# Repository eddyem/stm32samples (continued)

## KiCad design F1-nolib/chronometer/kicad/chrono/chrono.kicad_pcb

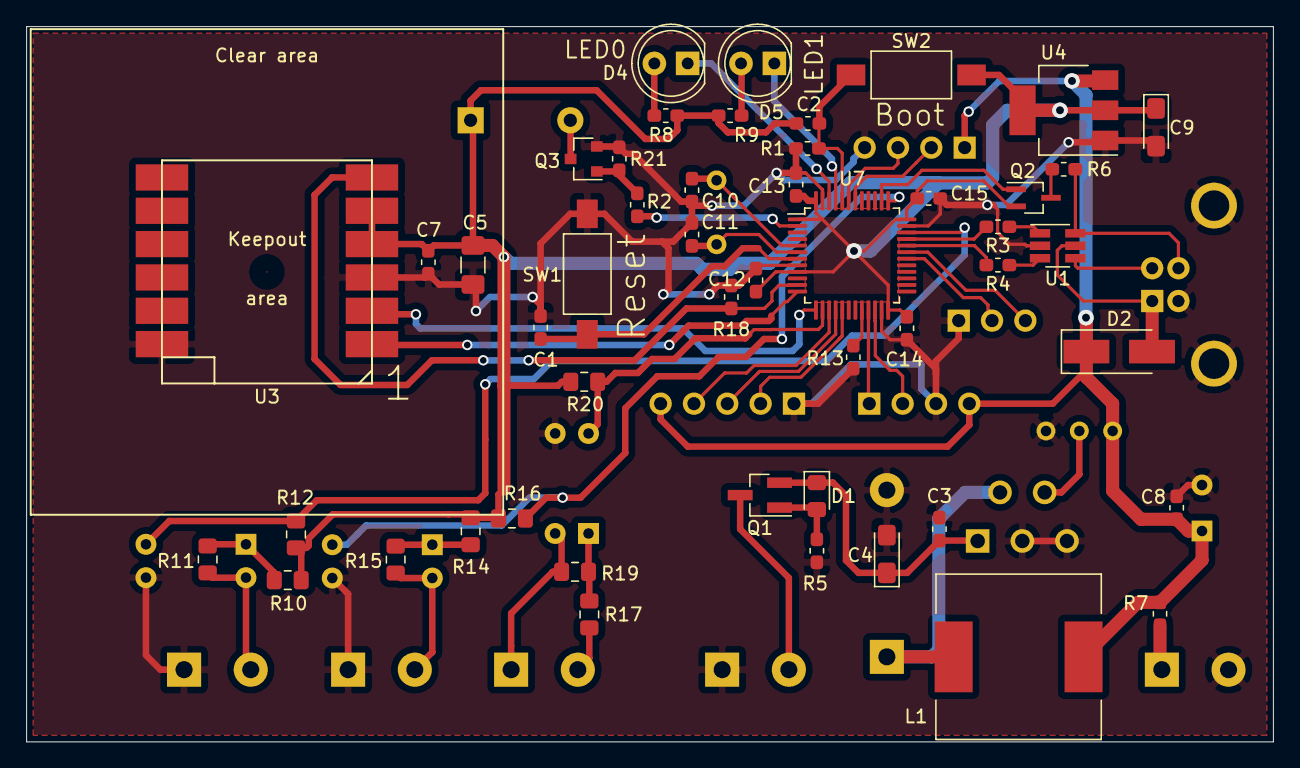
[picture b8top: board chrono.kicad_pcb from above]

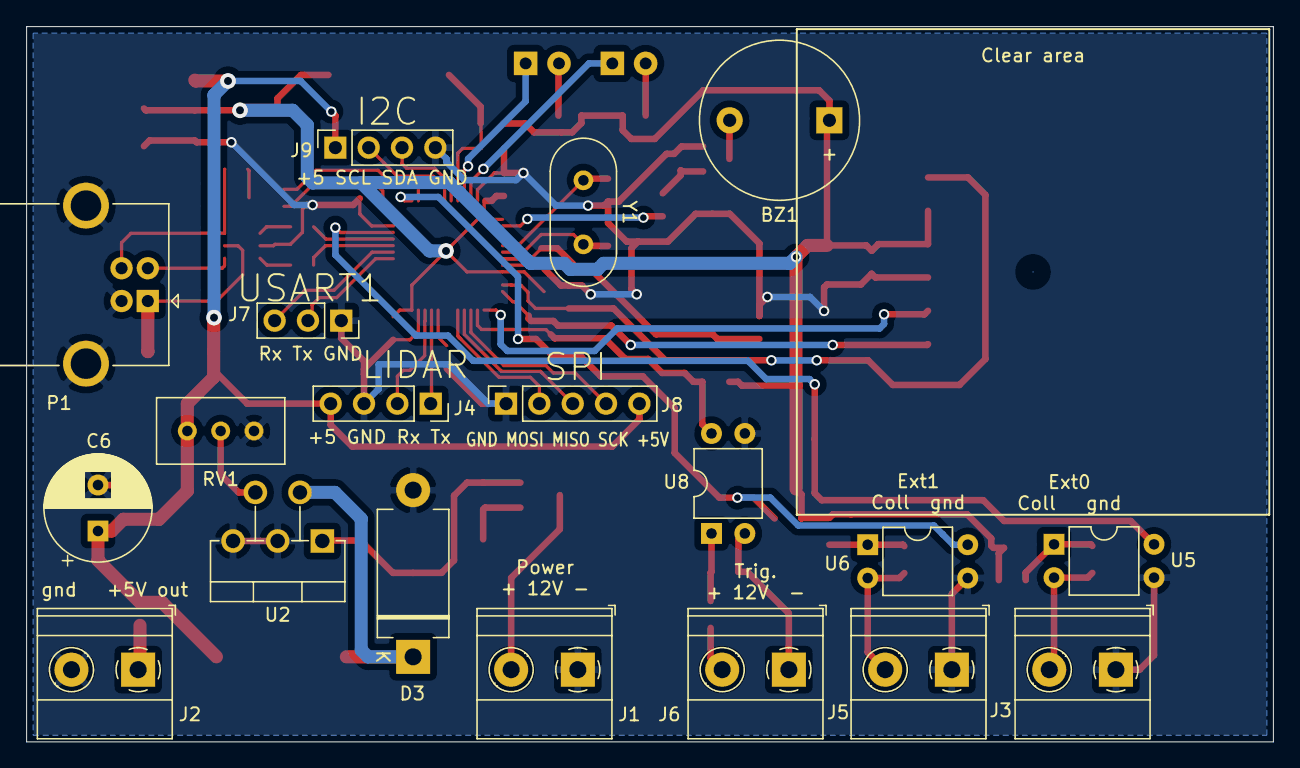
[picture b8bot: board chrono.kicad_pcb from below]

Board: 2 copper layers, 95.0 x 54.5 mm, 68 parts (19 on the bottom side), 52 nets.

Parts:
BZ1: Buzzer; Buzzer_12x9.5RM7.6
C1, C2, C3, C7, C8, C12, C13, C14, C15: 0.1; C_0603_1608Metric_Pad1.05x0.95mm_HandSolder
C4, C9: 47u; CP_EIA-3216-18_Kemet-A_Pad1.58x1.35mm_HandSolder
C5: 10u; C_1206_3216Metric_Pad1.42x1.75mm_HandSolder
C6: 100u; CP_Radial_D8.0mm_P3.50mm
C10, C11: 12; C_0603_1608Metric_Pad1.05x0.95mm_HandSolder
D1: MM3Z7V5; D_0805_2012Metric_Pad1.15x1.40mm_HandSolder
D2: SS14; D_SMA_Handsoldering
D3: 1n5822; D_DO-201_P12.70mm_Horizontal
D4: LED0; LED_D5.0mm
D5: LED1; LED_D5.0mm
J1: Power 12V; TerminalBlock_Phoenix_MKDS-1,5-2-5.08_1x02_P5.08mm_Horizont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
J2: +5Vout; TerminalBlock_Phoenix_MKDS-1,5-2-5.08_1x02_P5.08mm_Horizont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
J3: Ext_trig0; TerminalBlock_Phoenix_MKDS-1,5-2-5.08_1x02_P5.08mm_Horizont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
J4: LIDAR; PinSocket_1x04_P2.54mm_Vertical
J5: Ext_trig1; TerminalBlock_Phoenix_MKDS-1,5-2-5.08_1x02_P5.08mm_Horizont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
J6: Ext_trig2; TerminalBlock_Phoenix_MKDS-1,5-2-5.08_1x02_P5.08mm_Horizont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
J7: USART1; PinSocket_1x03_P2.54mm_Vertical
J8: SPI; PinSocket_1x05_P2.54mm_Vertical
J9: I2C1; PinSocket_1x04_P2.54mm_Vertical
L1: 100u; L_12x12mm_H4.5mm
P1: USB_B; USB_B_OST_USB-B1HSxx_Horizontal
Q1: AO3407; SOT-23_Handsoldering
Q2: DTA114Y; SOT-323_SC-70_Handsoldering
Q3: Q_NMOS_GSD; SOT-23
R1, R5, R21: 10k; R_0603_1608Metric_Pad1.05x0.95mm_HandSolder
R2: 510; R_0603_1608Metric_Pad1.05x0.95mm_HandSolder
R3, R4, R7: 22; R_0603_1608Metric_Pad1.05x0.95mm_HandSolder
R6: 1k5; R_0603_1608Metric_Pad1.05x0.95mm_HandSolder
R8, R9: 330; R_0603_1608Metric_Pad1.05x0.95mm_HandSolder
R10, R14: 330; R_0805_2012Metric_Pad1.15x1.40mm_HandSolder
R11, R12, R15, R16, R19, R20: 4k7; R_0805_2012Metric_Pad1.15x1.40mm_HandSolder
R13, R18: 100k; R_0603_1608Metric_Pad1.05x0.95mm_HandSolder
R17: 2k2; R_0805_2012Metric_Pad1.15x1.40mm_HandSolder
RV1: 10k; Potentiometer_Bourns_3296W_Vertical
SW1: Reset; SW_SPST_FSMSM
SW2: Boot; SW_SPST_FSMSM
U1: USBLC6-2SC6; SOT-23-6_Handsoldering
U2: LM2576ADJ; TO-220-5_P3.4x3.7mm_StaggerEven_Lead3.8mm_Vertical
U3: L80-R
U4: LM1117-3.3; SOT-223
U5, U6, U8: PC817; DIP-4_W7.62mm
U7: STM32F103C6Tx; LQFP-48_7x7mm_P0.5mm
Y1: 8MHz; Crystal_HC49-U_Vertical

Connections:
+3V3: BZ1.1, C2.2, C5.2, C7.2, C9.1, C12.2, C13.2, C14.2, C15.2, Q2.2, R8.2, R9.2, R10.2, R12.1, R14.2, R16.1, R20.1, SW2.2, U3.4, U3.5, U4.2, U4.4, U7.1, U7.9, U7.24, U7.36, U7.48
+5V: C6.1, C8.1, D2.1, J4.4, J8.5, J9.1, L1.1, R7.2, RV1.1, U4.3
/BOOT0: C2.1, R1.1, SW2.1, U7.44
/LED0: D4.1, U7.46
/LED1: D5.1, U7.45
/MISO: J8.3, U7.16
/MOSI: J8.2, U7.17
/NRST: C1.1, SW1.1, U7.7
/OSC_IN: C10.1, U7.5, Y1.1
/OSC_OUT: C11.1, U7.6, Y1.2
/PPS: R18.2, U3.6, U7.11
/SCK: J8.4, U7.15
/SCL: J9.2, U7.42
/SDA: J9.3, U7.43
/TRIG0: R12.2, U5.4, U7.34
/TRIG1: R16.2, U6.4, U7.37
/TRIG2: R20.2, U7.14, U8.4
/U1Rx: J7.3, U7.31
/U1Tx: J7.2, U7.30
/U2Rx: J4.2, U7.22
/U2Tx: J4.1, U7.21
/U3Rx: U3.2, U7.13
/U3Tx: U3.1, U7.12
/USBDM: R4.2, U7.32
/USBDP: R3.2, U7.33
/USB_PU: Q2.1, U7.38
/buzzer: R2.2, U7.2
GND: C1.2, C3.2, C4.2, C5.1, C6.2, C7.1, C8.2, C9.2, C10.2, C11.2, C12.1, C13.1, C14.1, C15.1, D3.2, J1.1, J2.2, J3.1, J4.3, J5.1, J7.1, J8.1, J9.4, P1.4, P1.5, Q3.2, R1.2, R5.1, R13.2, R18.1, R21.2, RV1.3, SW1.2, U1.2, U2.3, U2.5, U3.3, U3.12, U4.1, U5.3, U6.3, U7.8, U7.23, U7.35, U7.47, U8.3
unnamed: BZ1.2, Q3.3
unnamed: C3.1, C4.1, D1.1, Q1.2, U2.1
unnamed: D1.2, Q1.1, R5.2
unnamed: D2.2, P1.1, U1.5
unnamed: D3.1, L1.2, U2.2
unnamed: D4.2, R8.1
unnamed: D5.2, R9.1
unnamed: J1.2, Q1.3
unnamed: J2.1, R7.1
unnamed: J3.2, R11.1, U5.2
unnamed: J5.2, R15.1, U6.2
unnamed: J6.1, R19.1, U8.2
unnamed: J6.2, R17.1
unnamed: P1.2, U1.4
unnamed: P1.3, R6.2, U1.6
unnamed: Q2.3, R6.1
unnamed: Q3.1, R2.1, R21.1
unnamed: R3.1, U1.1
unnamed: R4.1, U1.3
unnamed: R10.1, R11.2, U5.1
unnamed: R13.1, U7.20
unnamed: R14.1, R15.2, U6.1
unnamed: R17.2, R19.2, U8.1
unnamed: RV1.2, U2.4

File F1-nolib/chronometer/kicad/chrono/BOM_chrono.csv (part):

"Source:","/home/eddy/Docs/SAO/ELECTRONICS/STM32/F1-srcs/chronometer/kicad/chrono/chrono.sch"
"Date:","÷Ô 09 ÉÀÌ 2019 08:40:12"
"Tool:","Eeschema (6.0.0-rc1-dev-1613-ga55d9819b)"
"Generator:","/usr/local/share/kicad/plugins/bom_csv_grouped_by_value.py"
"Component Count:","68"

"Individual Components:"

"Item","Qty","Reference(s)","Value","LibPart","Footprint","Datasheet","Manufacturer"
"","","BZ1","Buzzer","Device:Buzzer","Buzzer_Beeper:Buzzer_12x9.5RM7.6","~",""
"","","C1","0.1","stm32-rescue:C","Capacitor_SMD:C_0603_1608Metric_Pad1.05x0.95mm_HandSolder","",""
"","","C2","0.1","stm32-rescue:C","Capacitor_SMD:C_0603_1608Metric_Pad1.05x0.95mm_HandSolder","",""
"","","C3","0.1","stm32-rescue:C","Capacitor_SMD:C_0603_1608Metric_Pad1.05x0.95mm_HandSolder","",""
"","","C4","47u","stm32-rescue:CP","Capacitor_Tantalum_SMD:CP_EIA-3216-18_Kemet-A_Pad1.58x1.35mm_HandSolder","",""
"","","C5","10u","Device:C","Capacitor_SMD:C_1206_3216Metric_Pad1.42x1.75mm_HandSolder","~",""
"","","C6","100u","stm32-rescue:CP","Capacitor_THT:CP_Radial_D8.0mm_P3.50mm","",""
"","","C7","0.1","stm32-rescue:C","Capacitor_SMD:C_0603_1608Metric_Pad1.05x0.95mm_HandSolder","",""
"","","C8","0.1","stm32-rescue:C","Capacitor_SMD:C_0603_1608Metric_Pad1.05x0.95mm_HandSolder","",""
"","","C9","47u","stm32-rescue:CP","Capacitor_Tantalum_SMD:CP_EIA-3216-18_Kemet-A_Pad1.58x1.35mm_HandSolder","",""
"","","C10","12","stm32-rescue:C","Capacitor_SMD:C_0603_1608Metric_Pad1.05x0.95mm_HandSolder","",""
"","","C11","12","stm32-rescue:C","Capacitor_SMD:C_0603_1608Metric_Pad1.05x0.95mm_HandSolder","",""
"","","C12","0.1","stm32-rescue:C","Capacitor_SMD:C_0603_1608Metric_Pad1.05x0.95mm_HandSolder","",""
"","","C13","0.1","stm32-rescue:C","Capacitor_SMD:C_0603_1608Metric_Pad1.05x0.95mm_HandSolder","",""
"","","C14","0.1","stm32-rescue:C","Capacitor_SMD:C_0603_1608Metric_Pad1.05x0.95mm_HandSolder","",""
"","","C15","0.1","stm32-rescue:C","Capacitor_SMD:C_0603_1608Metric_Pad1.05x0.95mm_HandSolder","",""
"","","D1","MM3Z7V5","Device:D_Zener","Diode_SMD:D_0805_2012Metric_Pad1.15x1.40mm_HandSolder","~",""
"","","D2","SS14","Device:D_Schottky","Diode_SMD:D_SMA_Handsoldering","~",""
"","","D3","1n5822","stm32-rescue:D","Diode_THT:D_DO-201_P12.70mm_Horizontal","",""
"","","D4","LED0","stm32-rescue:LED-RESCUE-stm32","LED_THT:LED_D5.0mm","",""
"","","D5","LED1","stm32-rescue:LED-RESCUE-stm32","LED_THT:LED_D5.0mm","",""
"","","J1","Power 12V","Connector_Generic:Conn_01x02","TerminalBlock_Phoenix:TerminalBlock_Phoenix_MKDS-1,5-2-5.08_1x02_P5.08mm_Horizontal","~",""
"","","J2","+5Vout","Connector_Generic:Conn_01x02","TerminalBlock_Phoenix:TerminalBlock_Phoenix_MKDS-1,5-2-5.08_1x02_P5.08mm_Horizontal","~",""
"","","J3","Ext_trig0","Connector_Generic:Conn_01x02","TerminalBlock_Phoenix:TerminalBlock_Phoenix_MKDS-1,5-2-5.08_1x02_P5.08mm_Horizontal","~",""
"","","J4","LIDAR","Connector:Conn_01x04_Female","Connector_PinSocket_2.54mm:PinSocket_1x04_P2.54mm_Vertical","~",""
"","","J5","Ext_trig1","Connector_Generic:Conn_01x02","TerminalBlock_Phoenix:TerminalBlock_Phoenix_MKDS-1,5-2-5.08_1x02_P5.08mm_Horizontal","~",""
"","","J6","Ext_trig2","Connector_Generic:Conn_01x02","TerminalBlock_Phoenix:TerminalBlock_Phoenix_MKDS-1,5-2-5.08_1x02_P5.08mm_Horizontal","~",""
"","","J7","USART1","Connector:Conn_01x03_Female","Connector_PinSocket_2.54mm:PinSocket_1x03_P2.54mm_Vertical","~",""
"","","J8","SPI","Connector:Conn_01x05_Female","Connector_PinSocket_2.54mm:PinSocket_1x05_P2.54mm_Vertical","~",""
"","","J9","I2C1","Connector:Conn_01x04_Female","Connector_PinSocket_2.54mm:PinSocket_1x04_P2.54mm_Vertical","~",""
"","","L1","100u","stm32-rescue:L","Inductor_SMD:L_12x12mm_H4.5mm","",""
"","","P1","USB_B","stm32-rescue:USB_A-RESCUE-stm32","Connectors_USB:USB_B_OST_USB-B1HSxx_Horizontal","",""
"","","Q1","AO3407","stm32-rescue:Q_PMOS_GSD","TO_SOT_Packages_SMD:SOT-23_Handsoldering","",""
"","","Q2","DTA114Y","Transistor_BJT:DTA114Y","TO_SOT_Packages_SMD:SOT-323_SC-70_Handsoldering","",""
"","","Q3","Q_NMOS_GSD","Device:Q_NMOS_GSD","Package_TO_SOT_SMD:SOT-23","~",""
"","","R1","10k","stm32-rescue:R","Resistor_SMD:R_0603_1608Metric_Pad1.05x0.95mm_HandSolder","",""
"","","R2","510","Device:R","Resistor_SMD:R_0603_1608Metric_Pad1.05x0.95mm_HandSolder","~",""
"","","R3","22","stm32-rescue:R","Resistor_SMD:R_0603_1608Metric_Pad1.05x0.95mm_HandSolder","",""
"","","R4","22","stm32-rescue:R","Resistor_SMD:R_0603_1608Metric_Pad1.05x0.95mm_HandSolder","",""
"","","R5","10k","stm32-rescue:R","Resistor_SMD:R_0603_1608Metric_Pad1.05x0.95mm_HandSolder","",""
"","","R6","1k5","stm32-rescue:R","Resistor_SMD:R_0603_1608Metric_Pad1.05x0.95mm_HandSolder","",""
"","","R7","22","Device:R","Resistor_SMD:R_0603_1608Metric_Pad1.05x0.95mm_HandSolder","~",""
"","","R8","330","stm32-rescue:R","Resistor_SMD:R_0603_1608Metric_Pad1.05x0.95mm_HandSolder","",""
"","","R9","330","stm32-rescue:R","Resistor_SMD:R_0603_1608Metric_Pad1.05x0.95mm_HandSolder","",""
"","","R10","330","Device:R","Resistor_SMD:R_0805_2012Metric_Pad1.15x1.40mm_HandSolder","~",""
"","","R11","4k7","Device:R","Resistor_SMD:R_0805_2012Metric_Pad1.15x1.40mm_HandSolder","~",""
"","","R12","4k7","Device:R","Resistor_SMD:R_0805_2012Metric_Pad1.15x1.40mm_HandSolder","~",""
"","","R13","100k","stm32-rescue:R","Resistor_SMD:R_0603_1608Metric_Pad1.05x0.95mm_HandSolder","",""
"","","R14","330","Device:R","Resistor_SMD:R_0805_2012Metric_Pad1.15x1.40mm_HandSolder","~",""
"","","R15","4k7","Device:R","Resistor_SMD:R_0805_2012Metric_Pad1.15x1.40mm_HandSolder","~",""
"","","R16","4k7","Device:R","Resistor_SMD:R_0805_2012Metric_Pad1.15x1.40mm_HandSolder","~",""
"","","R17","2k2","Device:R","Resistor_SMD:R_0805_2012Metric_Pad1.15x1.40mm_HandSolder","~",""
"","","R18","100k","stm32-rescue:R","Resistor_SMD:R_0603_1608Metric_Pad1.05x0.95mm_HandSolder","",""
"","","R19","4k7","Device:R","Resistor_SMD:R_0805_2012Metric_Pad1.15x1.40mm_HandSolder","~",""
"","","R20","4k7","Device:R","Resistor_SMD:R_0805_2012Metric_Pad1.15x1.40mm_HandSolder","~",""
"","","R21","10k","Device:R","Resistor_SMD:R_0603_1608Metric_Pad1.05x0.95mm_HandSolder","~",""
"","","RV1","R_POT","Device:R_POT","Potentiometer_THT:Potentiometer_Bourns_3296W_Vertical","~",""
"","","SW1","Reset","Switch:SW_Push","Buttons_Switches_SMD:SW_SPST_FSMSM","",""
"","","SW2","Boot","Switch:SW_Push","Buttons_Switches_SMD:SW_SPST_FSMSM","",""
"","","U1","USBLC6-2SC6","Power_Protection:USBLC6-2SC6","TO_SOT_Packages_SMD:SOT-23-6_Handsoldering","http://www2.st.com/resource/en/datasheet/CD00050750.pdf",""
"","","U2","LM2576ADJ","stm32-rescue:LM2576HV","TO_SOT_Packages_THT:TO-220-5_P3.4x3.7mm_StaggerEven_Lead3.8mm_Vertical","","Texas Instruments"
"","","U3","L80-R","Chrono:L80-R","chrono:L80-R","",""
"","","U4","LM1117-3.3","stm32-rescue:LM1117-3.3-RESCUE-stm32","TO_SOT_Packages_SMD:SOT-223","",""
"","","U5","PC817","Isolator:PC817","Package_DIP:DIP-4_W7.62mm","http://www.soselectronic.cz/a_info/resource/d/pc817.pdf",""
"","","U6","PC817","Isolator:PC817","Package_DIP:DIP-4_W7.62mm","http://www.soselectronic.cz/a_info/resource/d/pc817.pdf",""
"","","U7","STM32F103C6Tx","MCU_ST_STM32F1:STM32F103C6Tx","Package_QFP:LQFP-48_7x7mm_P0.5mm","http://www.st.com/st-web-ui/static/active/en/resource/techni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",""
"","","U8","PC817","Isolator:PC817","Package_DIP:DIP-4_W7.62mm","http://www.soselectronic.cz/a_info/resource/d/pc817.pdf",""
"","","Y1","8MHz","Device:Crystal","Crystal:Crystal_HC49-U_Vertical","~",""



"Collated Components:"

"Item","Qty","Reference(s)","Value","LibPart","Footprint","Datasheet","Manufacturer"
"1","1","BZ1","Buzzer","Device:Buzzer","Buzzer_Beeper:Buzzer_12x9.5RM7.6","~",""
"2","9","C1, C2, C3, C7, C8, C12, C13, C14, C15","0.1","stm32-rescue:C","Capacitor_SMD:C_0603_1608Metric_Pad1.05x0.95mm_HandSolder","",""
"3","2","C4, C9","47u","stm32-rescue:CP","Capacitor_Tantalum_SMD:CP_EIA-3216-18_Kemet-A_Pad1.58x1.35mm_HandSolder","",""
"4","1","C5","10u","Device:C","Capacitor_SMD:C_1206_3216Metric_Pad1.42x1.75mm_HandSolder","~",""
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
